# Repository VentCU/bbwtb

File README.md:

# VentCU
> A radically accessible, affordable, and producible ventilator. 

## VentCU has not been clinically tested. It is NOT approved for medical use.

## What is VentCU?
In response to the initial explosion in demand for ventilators caused by the global COVID-19 crisis, VentCU was developed as an intermediary manual ventilation device for clinical use.  Designed in collaboration with medical professionals and skilled engineers, VentCU is positioned as a **radically affordable** device able to be **assembled with no prior experience and no specialized tools**.  *Constructed entirely from consumer-off-the-shelf parts*, available in the hundreds to thousands in a matter of days, hospital technicians and maker enthusiasts alike will be able to construct VentCU with nothing more than an instruction manual, an Allen key, a pair of scissors, and a soldering iron.

The critical demand for ventilators that sparked VentCU’s conception has thankfully subsided since the beginning of the COVID-19 crisis.  However, VentCU continues as an area of research to be used in further development of affordable, easily manufacturable ventilators should another surge for ventilators emerge or for communities already lacking access to proper ventilation devices.  **As such, VentCU is completely open-source.**

## [VentCU Website](https://coda.io/@maker/ventcu) 
Check out our website (https://coda.io/@maker/ventcu) for detailed technical, BOM, and contact information.
Also, feel free to share our work on social media!

# Repository Structure
> `version 0.1-alpha`
How to install the repo in an open terminal window on your VentCU device's Raspberry Pi 3 B+:
```
cd $HOME
mkdir Workspace
cd Workspace
git clone https://github.com/VentCU/bbwtb.git
```

## Electronics
An electronics layout and next-generation PCB of the VentCU device is viewable in the `electronics` directory. 

## Mechanics
A stable release of the VentCU device main assembly can be found within the `mechanics` directory. A viewable, online CAD model with complete relationships can viewed at this [Onshape link](https://cad.onshape.com/documents/f7de46ca7dc3a8d28aa71883/w/2f9839ab30d7aa3f0e55734c/e/351b5eba45a0f5e74e63c1ba).

A user manual and specification sheet can be found in the stable release directory in the `mechanics` directory and viewed online at this [Google Docs link](https://docs.google.com/document/d/146-ZcDFsmwu9b4q7zNh3ngux9tSg6TSOEBYOS_3Alh4/edit?usp=sharing)

## Media
CAD renders and real-life pictures of the VentCU device can be viewed in the `media` directory.

## Software
The software repository contains code to run the VentCU device and instructions for installation. See `software\README.md` for a comprehensive system breakdown. 

## Repository Changelog
Newest on top.
09/12/2020: `version-0.1-alpha`: preliminary alpha release for first public publishing
09/03/2020: `version-0.0-alpha`: stable alpha for committee demo
### bbwtb

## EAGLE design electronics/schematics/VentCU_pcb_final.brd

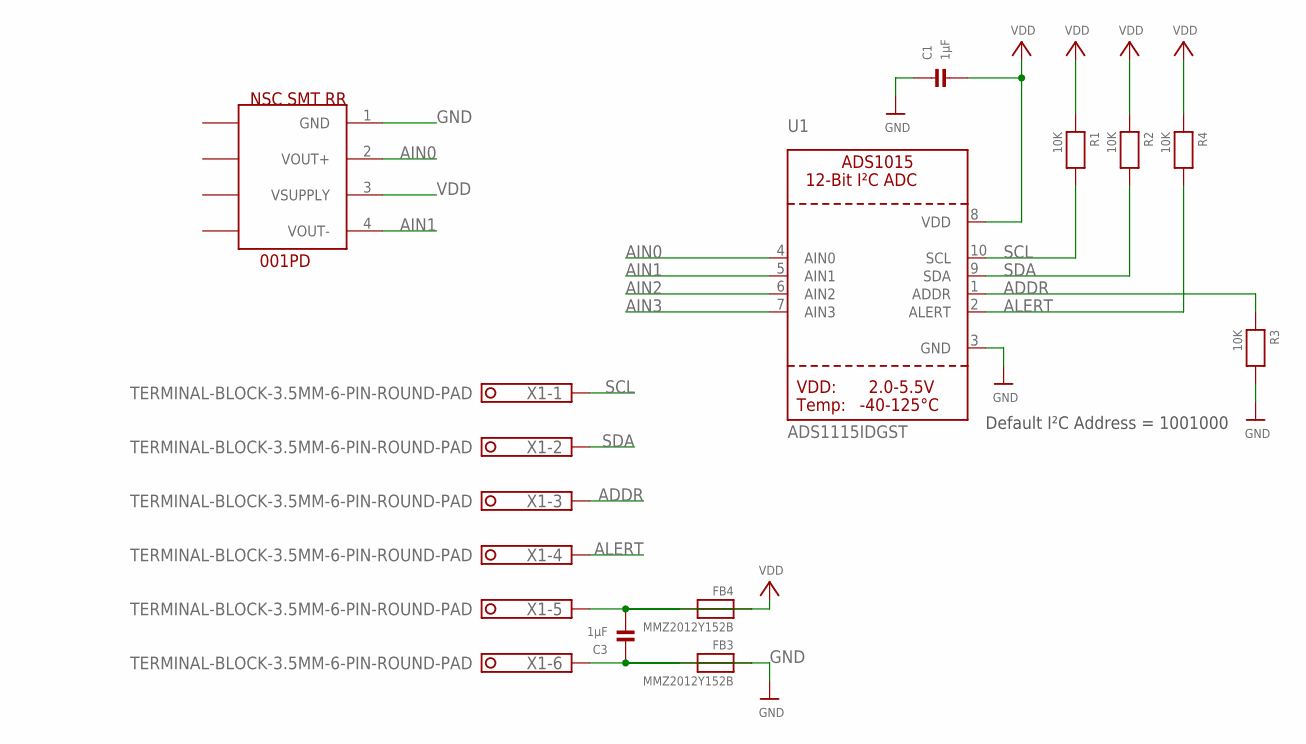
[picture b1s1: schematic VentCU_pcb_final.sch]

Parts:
C1, C3: 1µF; 0805
FB3, FB4: MMZ2012Y152B; 0805
R1, R2, R3, R4: 10K; 0805
U1: ADS1115IDGST; MSOP10
U$1: NSC-M
X1: TERMINAL-BLOCK-3.5MM-6-PIN-ROUND-PAD; TERMINAL-BLOCK-6-PIN-3.5MM-ROUND-PAD

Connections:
ADDR: R3.1, U1.1 (ADDR), X1.3
AIN0: U1.4 (AIN0), U$1.2 (VOUT+)
AIN1: U1.5 (AIN1), U$1.4 (VOUT-)
AIN2: U1.6 (AIN2)
AIN3: U1.7 (AIN3)
ALERT: R4.2, U1.2 (ALERT), X1.4
GND: C1.1, C3.1, FB3.1, R3.2, U1.3 (GND), U$1.1 (GND)
unnamed: FB4.2, X1.5
unnamed: FB3.2, X1.6
SCL: R1.2, U1.10 (SCL), X1.1
SDA: R2.2, U1.9 (SDA), X1.2
VDD: C1.2, C3.2, FB4.1, R1.1, R2.1, R4.1, U1.8 (VDD), U$1.3 (VSUPPLY)

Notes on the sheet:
Default I²C Address = 1001000

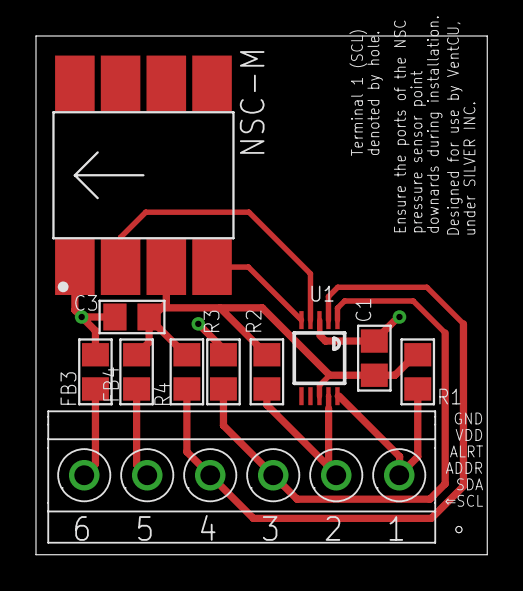
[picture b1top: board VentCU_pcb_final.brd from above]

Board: 2 copper layers, 25.1 x 28.8 mm, 11 parts (0 on the bottom side), 10 nets.

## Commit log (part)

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2020-04-07 CAD files and image documentation uploaded
2020-04-07 added main assembly
2020-05-03 updated CAD models to match submission design
2020-05-03 added control diagrams
2020-05-03 added software planning document
2020-05-08 basic control system code structure added
2020-05-08 tic motor controller python classes added
2020-05-08 tic motor controller python example scripts added
2020-05-11 added sensor scripts (empty)
2020-05-11 added rotary encoder script
    ( please test @badinkajink ) thanks
2020-05-15 limited switch class added
2020-05-15 pressure sensor class added
    needs to be tested
2020-05-15 added set max speed and set starting speed
    tic motor controller. Please test @badinkajink
2020-05-15 minor changes
2020-05-16 tic serial (usb) example script working
2020-05-16 updated scripts that deps on ticUSB class
2020-05-16 turned rotary encoder script into class
    badly needs to be tested
2020-05-16 added new encoder code
2020-05-17 added scroll graph example
2020-05-17 added close loop control test script
    not complete
2020-05-17 updated mock UI
2020-05-17 Setup plots and refreshing with random data
2020-05-17 updated mock ui, hide the butthons, added some color
2020-05-17 Add edit parameters window
2020-05-17 Fix previous merge error
2020-05-18 close loop test 2 finished, working
2020-05-18 Add limit switch test code
2020-05-18 added simple PID controller & test
2020-05-18 tested limit switch
2020-05-18 reorganized some control system files
2020-05-18 PID controller working, can bring motor to a state.
2020-05-18 pid control test finished and working
2020-05-18 updated motor controller script
2020-05-19 Begin stack structure plan: ventilator class, motor class, gpio map, move gui
2020-05-19 Correct rotatory/rotator typo
2020-05-19 added new encoder code, better performance, not good enough
2020-05-19 updated the naming for tic_usb and encoder
    the new scripts should be fully integrated.
    the old scripts should have `old` appended to their names.
    fixed conflict in pid_control_test
2020-05-19 moved gpio_map to the configs module, other small changes
2020-05-19 updated controller script, added homing procedure and test
2020-05-19 Re-work stack: encoder, motor, controller, ventilator
    - Integrated callback into RotaryEncoder
    - Switched RotaryEncoder logic to NC and added contacted function
    - Flushed out Motor class
    - Switched VentilatorController class to use a Motor
    - Added VentilatorController to Ventilator class
2020-05-19 integrated pid with motor class
2020-05-19 removed not used imports, updated indentations, improved formatting.
2020-05-19 added a unit test for the motor class. cleaned up some old tests
2020-05-19 added contact limit switch gpio port
2020-05-21 Fix homing bugs; it works!
2020-05-21 renamed tic device object, added set pose method
2020-05-21 cleaning up
2020-05-21 motor movement code added
2020-05-21 basic arm movement script added
2020-05-23 parameterized bpm and got constant
2020-05-23 added signal handling for a safer exit
2020-05-24 Modified appearance
2020-05-24 Created UI files
2020-05-24 Rename README.txt to documentation.txt
2020-05-26 converted documentation to markdown readme
2020-05-26 started native qtcreator app and imported .ui files within gui folder, separate testbed basically
2020-05-26 added gui README
2020-05-26 fixed ui screen size
2020-05-26 organized file structure and README
2020-05-26 removed accidental legacy files, oops
2020-05-26 oops again, added back legacy files
2020-05-26 updated software documentation
2020-05-26 Add window stack and basic window navigation
2020-05-26 Split window navigation setup into function
2020-05-28 Minor sizing changes
2020-05-28 Add some FSM code to the vent. controller
2020-05-28 Add main ventilator controller FSM, util funcs, consts, and many TODOS
2020-05-28 Begin ui_controller_interface
2020-05-28 remove "break" in the if statements
    the use of break outside of loop is undefined in python
2020-05-28 add minor improvements to the home() method
    add error checking for state machine safety. other small changes for code improvement.
2020-05-30 Scaffold alarm handling
2020-05-30 change how lambda function is implemented in controller interface
    a python lambda can only be a single expression
2020-05-30 make alarm a module and update method calls in ventilator class
2020-05-30 consolidate alarm classes init, add header comments
2020-05-30 implement sections of the FSM
    - also cleaned up some variables and added helper methods
2020-05-30 add some error handling and some documentation
2020-05-30 mapped buzzer gpio to gpio pin 25
2020-06-01 added pressure sensor unit test
2020-06-02 added gpio for power switch, test code for buzzer, integrated pressure sensor test script into class structure
2020-06-06 patch calculate_wave_form method
    now the method won't crash anything : )
2020-06-06 fix homing procedure bug
2020-06-08 Begin gui to control logic connections
2020-06-11 debugging ui_controller, just syntax errors so far
2020-06-11 Debug interface
2020-06-11 Fixed edit parameters screen button
2020-06-11 Fixed it edit parameters for real this time
2020-06-11 fixed 4 real 4 real
2020-06-11 debugging home call from gui
2020-06-11 Change UI label names
2020-06-11 Propegate unknown errors
2020-06-13 Fix edit_parameters UI titles
2020-06-13 Fix main_window UI titles
2020-06-13 extract start_homing method
2020-06-16 Modified UI design not final version yet
2020-06-20 Updated fonts
2020-06-20 wrapped state change signal and dummy qtobject to work with connect
2020-06-25 implemented Qt native threading
2020-06-27 added buzzer member to alarm_handler
2020-06-27 added configs sys path to alarm_handler
2020-06-28 fixed sys path imports in alarm_handler
2020-06-28 debugging sending nonetype to try_controller_method
2020-06-28 fixed calling a method instead of feeding as an object in try_controller_method
2020-06-28 Test two buzzers with beeping
2020-06-28 Show windows in full screen
2020-06-28 Stop motor if both switched hit while homing
2020-06-30 Added images (hopefully)
2020-06-30 Added house image
2020-06-30 Create start script
2020-07-02 Minor visual UI fixes
2020-07-02 Add logging for changing parameters
2020-07-02 Fix type error for print message
2020-07-02 added pressure sensor graphing, logging and some ventilator_controller debugging
2020-07-02 removed time constraints on ventilator_controller insp/exp states because time is a construct
2020-07-02 Add local parameters to interface for modification before confirmation
2020-07-02 Remove merge markers
2020-07-02 Fix default argument error
2020-07-02 added pressure sensor log
2020-07-02 Add continuous label modification
2020-07-02 Add dymanic element modification for parameters flow
2020-07-02 Modify comment types and whitespace for clarity
2020-07-02 Spawn thread for rehoming
2020-07-02 Reset homing direction on homing completion
2020-07-02 Pull with sudo
2020-07-02 Match title spacing
2020-07-02 Add volume graph and change colors
2020-07-03 create shutdown signal sender
2020-07-05 add power switch to ventilator class
2020-07-05 add power switch to ventilator controller
2020-07-05 create vc unit test
2020-07-05 fix missing self in method
2020-07-05 debugging calculate_waveform()
2020-07-05 updated debug
2020-07-05 it goes up and down now
2020-07-06 Trigger state change from off switch
2020-07-07 Scaffold move_to_encoder_pose_with_dur
2020-07-07 Add tester class
2020-07-07 Modify FSM homing logic
2020-07-07 Formatting cleanup
2020-07-07 Pause FSM with power_switch_callback
2020-07-07 Time is a construct
2020-07-07 Implement power switch
2020-07-07 Test basic time based control
2020-07-09 Development slider class.
2020-07-10 added slider widget to main gui, missing functionality
2020-07-12 adding max and min to tidal volume.
2020-07-12 test bpm, TV and adjust calculate wvform
    demonstrate that the bpm and tv variables work
    and also adjust waveform method to make it
    real-time
2020-07-14 Example for full size window
2020-07-18 added voltage plotting to pressure_sensor plotting script
2020-07-20 incorporated microseconds in subtract_seconds in calculate_waveform, potentially fixed issues
2020-07-23 UI interface instance variable to control thread spawning upon interface parameter changes ( BPM, etc.)
2020-07-24 set motor current and prev target based on fsm states in update_tidal_volume
    If in EXP_STATE or INSP_PAUSE_STATE, set current target to motor_upper_target
    and prev_target to motor_lower_target.
    Else, set current target to motor_lower_target and prev_target to motor_upper_target
2020-07-26 Add skeleton for logging structure
2020-07-30 Modify logger.py to wrap python native logging
    logger.py now simply wraps python logging as LoggerInit so that ventilator.py stays clean
2020-08-06 Add StreamHandler to logger basic config
2020-08-06 Replace print statements with logs
2020-08-06 Fix log message formatting
2020-08-08 Initial vernier api placement.
2020-08-09 vernier init commented.
2020-08-21 Removing Vernier.
2020-08-21 Implementing framework for alarm handling gui.
2020-08-21 Homing Alarm Handling completed. Gui widget shown on except_alarm_hook signal.
2020-08-23 Updating type(..) to isinstance(.., classinfo).
2020-08-23 Update alarm widget text framework.
2020-08-23 Verify IE control works and implement correct PID_TIME_SCALE_FACTOR values for different distances
2020-08-23 Connect alarm update text to UI popupwq
2020-08-23 Remove pycache file
2020-08-23 Implemented polynomially fitted PID scale factor through get_scale_factor(..).
2020-08-25 modify tic usb test to check that motor can meet max specification speed
2020-08-30 Tested poly function.
2020-08-30 I:E , BPM shows realtime on gui.
2020-08-31 rm doubles of *.ui
2020-09-01 Adding rehome button to alarm_condition.ui.
2020-09-01 Alarm hook calls PAUSE_STATE to be set.
2020-09-01 Updating with code that expresses that dismissed alarms require different widget redirection depending on state.
2020-09-01 Allowing controller object to access current_state attribute.
2020-09-01 connect gui close to motor destructor
2020-09-01 Connect gui close to controller stop ventilation rather than motor destructor
2020-09-01 Accessing the ui QtStack through ui_controller_interface for alarm handler.
2020-09-01 Saving last state to allow alarm to quickly set controller to pause state.
2020-09-03 Add true pressure sensor plotting to ui
2020-09-03 Extend y_axis of pressure sensor ui plot
2020-09-03 Changed font size for readout
2020-09-03 Added text wrapping
2020-09-03 Add logs directory and modify measured IE and BPM displayed values to round to int
2020-09-03 Add rounding for real for I:E
2020-09-03 Reverse I:E to match set I:E
2020-09-03 Modify get_raw_pressure to always return positive value
2020-09-03 Adjust code order to test plot settings application effect
2020-09-03 FIX FULL SCREEN...neil...
2020-09-03 Enable buzzer sounding on alarms
2020-09-03 Import sys to ventilator controller for import pathing
2020-09-03 Fix syntax assignment error on buzzers
2020-09-03 add under pressure alarm implementation
2020-09-03 pressure sensor one last try
2020-09-03 alarm last push
2020-09-03 take out pressure sensor and alarms for now
2020-09-12 Clean up file structure and move tests to /unit_tests
2020-09-12 Remove vernier go direct spirometer support files
2020-09-12 Remove deprecated software files
2020-09-13 update main assembly and move old one to new v2 directory
2020-09-13 update README and restructure mechanics repo into release versions
2020-09-13 Inserted manual link
2020-09-13 Added manual pdf
2020-09-13 correct code styling formatting in repo and software README
2020-09-13 more README cleanup to code syntax formatting
2020-09-13 remove deprecated documentation directory
2020-09-13 add setup-script for install python packages on first time setup
2020-09-13 Update READMEs
2020-09-13 add ui documentation
2020-09-13 update READMEs for specific software folders
2020-09-13 fix newline formatting in control_system/README
2020-10-23 pcb/schematic image upload
2020-10-23 board/schematic upload
2020-10-23 helpful libraries that informed the design
2020-10-23 custom components created for VentCU
2020-10-23 board uploaded with dimensions
